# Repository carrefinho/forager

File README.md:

# Forager

Forager is a Voyager-inspired 34-key low-profile wireless split keyboard powered by ZMK.

> why does the large Voyager not simply eat the small Forager?

## Design

- Condensed [ZSA Voyager](https://www.zsa.io/voyager) layout without outer pinkie column and number row
- Hot-swap Kailh Choc V1 switches in Choc (18x17mm) spacing with Voyager-esque switch puller grooves

- Wireless only with Seeed XIAO nRF52840 running ZMK firmware
- Magnetic tenting legs inspired by Voyager and [Unicorne](https://www.boardsource.xyz/products/unicorne)

- Compact silhouette without the usual blank space occupied by controller
- Fully enclosed with 3D-printed two-piece case
- Minimal BOM by utilizing XIAO nRF52840's onboard RGB LED and reset button

## Build Guide and Parts List

[Find the build guide here.](/docs/build-guide.md)

## Firmware

[Find the ZMK module here.](https://github.com/carrefinho/forager-zmk-module)

## Credits

- [ZSA Voyager](https://www.zsa.io/voyager): overall layout & aesthetics
- [GEIGEIGEIST/TOTEM](https://github.com/GEIGEIGEIST/TOTEM): XIAO PCB footprint and general placement
- [ebastler/marbastlib](https://github.com/ebastler/marbastlib): symbols and PCB footprints
- [caksoylar/zmk-rgbled-widget](https://github.com/caksoylar/zmk-rgbled-widget): RGB LED functionality

## Gallery

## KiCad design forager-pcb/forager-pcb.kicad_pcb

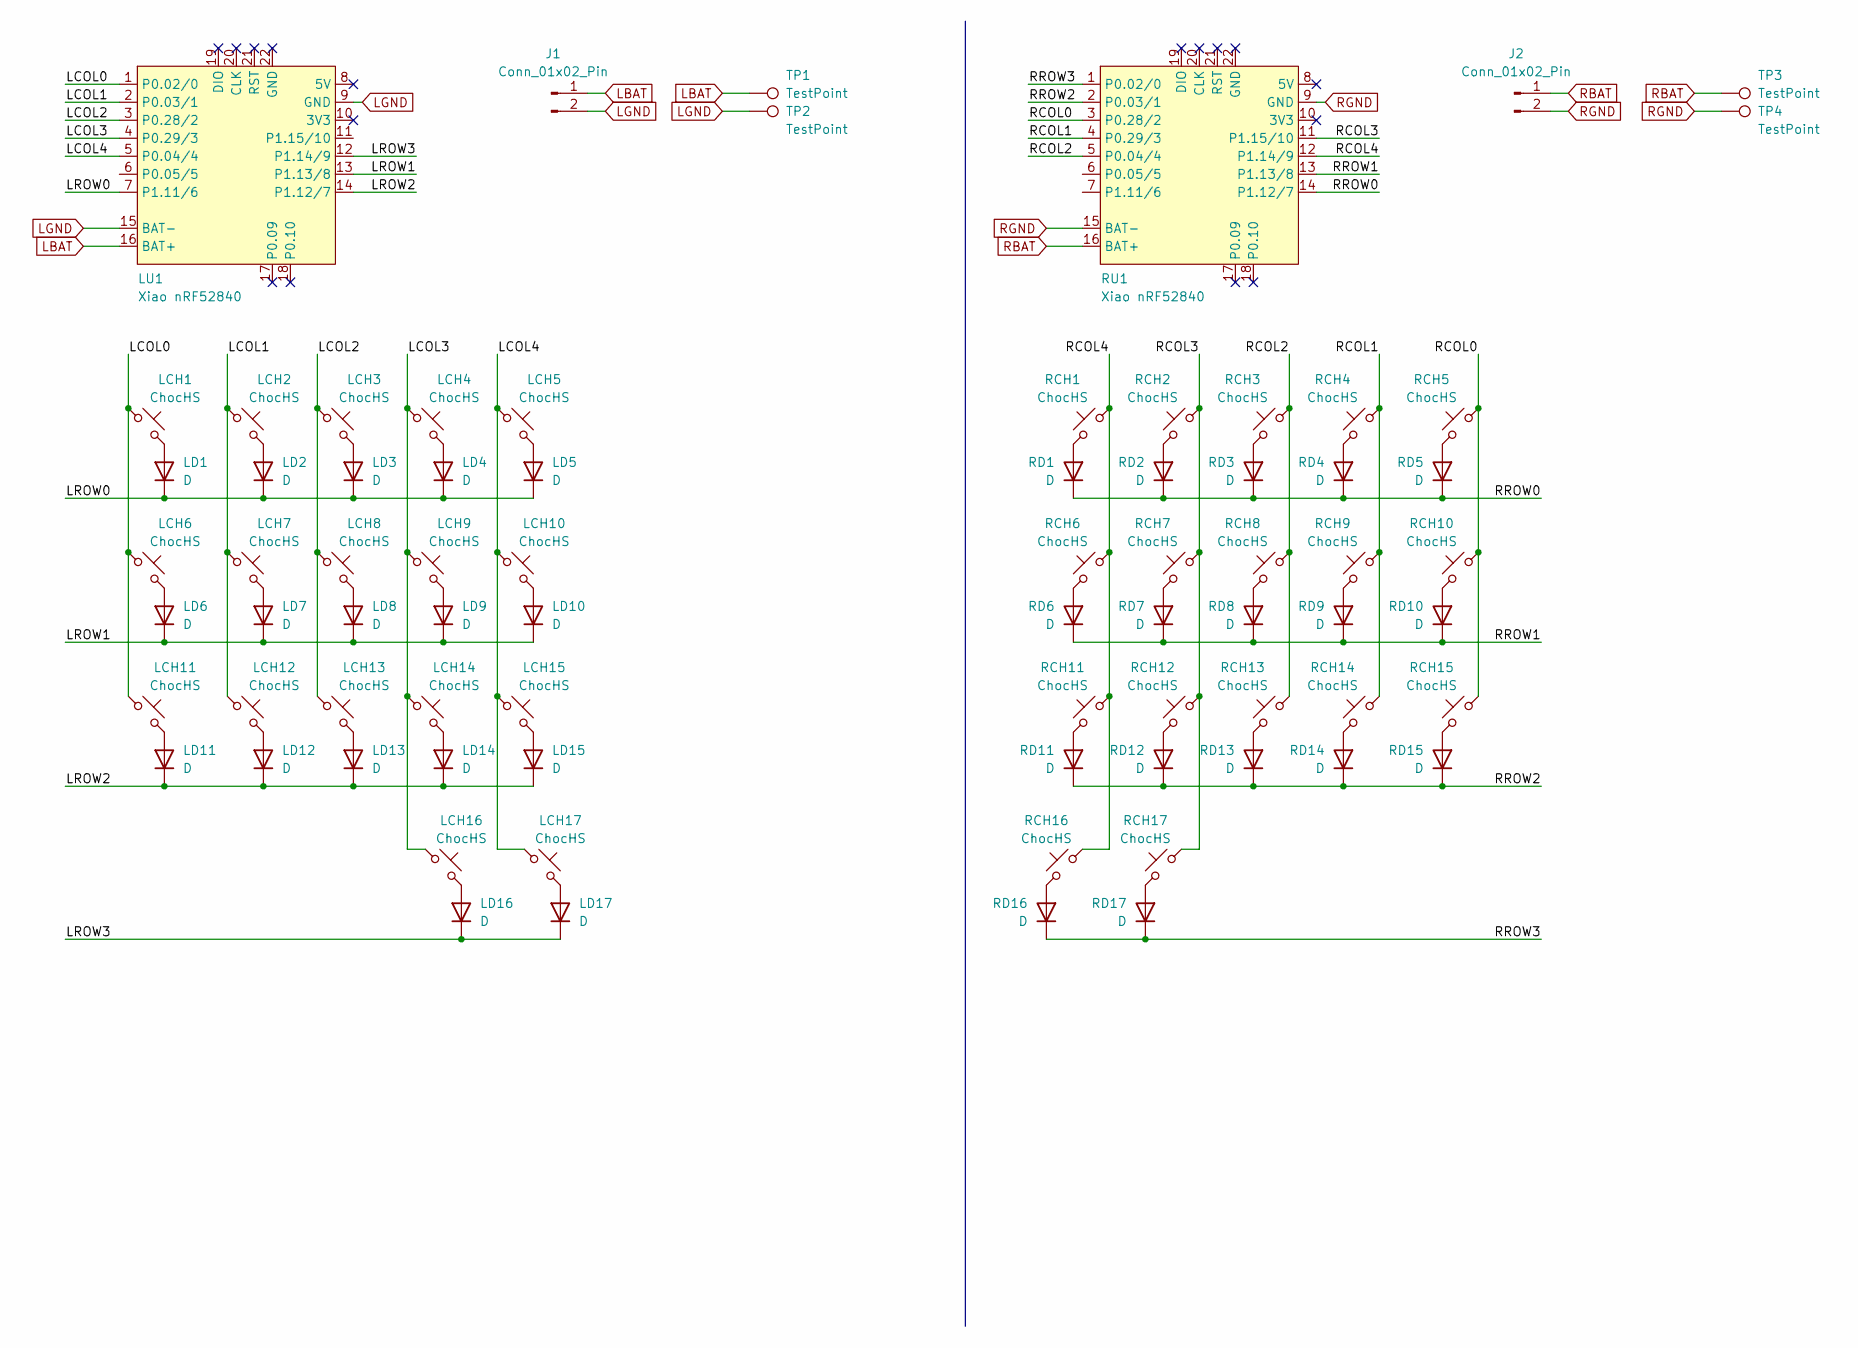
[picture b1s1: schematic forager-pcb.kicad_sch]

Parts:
J1, J2: Conn_01x02_Pin; JST_ACH_BM02B-ACHSS-GAN-ETF_1x02-1MP_P1.20mm_Vertical
LCH1, LCH2, LCH3, LCH4, LCH5, LCH6, LCH7, LCH8, LCH9, LCH10, LCH11, LCH12, LCH13, LCH14, LCH15, LCH16, LCH17: ChocHS; SW_choc_v1_HS_MBK
LD1, LD2, LD3, LD4, LD5, LD6, LD7, LD8, LD9, LD10, LD11, LD12, LD13, LD14, LD15, LD16, LD17: D; D_SOD-123
LU1: Xiao nRF52840; xiao-ble-smd-cutout
RCH1, RCH2, RCH3, RCH4, RCH5, RCH6, RCH7, RCH8, RCH9, RCH10, RCH11, RCH12, RCH13, RCH14, RCH15, RCH16, RCH17: ChocHS; SW_choc_v1_HS_MBK
RD1, RD2, RD3, RD4, RD5, RD6, RD7, RD8, RD9, RD10, RD11, RD12, RD13, RD14, RD15, RD16, RD17: D; D_SOD-123
RU1: Xiao nRF52840; xiao-ble-smd-cutout
TP1, TP2, TP3, TP4: TestPoint; TestPoint_Pad_D2.0mm

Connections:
/LCOL0: LCH1.1, LCH6.1, LCH11.1, LU1.1 (P0.02/0)
/LCOL1: LCH2.1, LCH7.1, LCH12.1, LU1.2 (P0.03/1)
/LCOL2: LCH3.1, LCH8.1, LCH13.1, LU1.3 (P0.28/2)
/LCOL3: LCH4.1, LCH9.1, LCH14.1, LCH16.1, LU1.4 (P0.29/3)
/LCOL4: LCH5.1, LCH10.1, LCH15.1, LCH17.1, LU1.5 (P0.04/4)
/LROW0: LD1.1 (K), LD2.1 (K), LD3.1 (K), LD4.1 (K), LD5.1 (K), LU1.7 (P1.11/6)
/LROW1: LD6.1 (K), LD7.1 (K), LD8.1 (K), LD9.1 (K), LD10.1 (K), LU1.13 (P1.13/8)
/LROW2: LD11.1 (K), LD12.1 (K), LD13.1 (K), LD14.1 (K), LD15.1 (K), LU1.14 (P1.12/7)
/LROW3: LD16.1 (K), LD17.1 (K), LU1.12 (P1.14/9)
/RCOL0: RCH5.1, RCH10.1, RCH15.1, RU1.3 (P0.28/2)
/RCOL1: RCH4.1, RCH9.1, RCH14.1, RU1.4 (P0.29/3)
/RCOL2: RCH3.1, RCH8.1, RCH13.1, RU1.5 (P0.04/4)
/RCOL3: RCH2.1, RCH7.1, RCH12.1, RCH17.1, RU1.11 (P1.15/10)
/RCOL4: RCH1.1, RCH6.1, RCH11.1, RCH16.1, RU1.12 (P1.14/9)
/RROW0: RD1.1 (K), RD2.1 (K), RD3.1 (K), RD4.1 (K), RD5.1 (K), RU1.14 (P1.12/7)
/RROW1: RD6.1 (K), RD7.1 (K), RD8.1 (K), RD9.1 (K), RD10.1 (K), RU1.13 (P1.13/8)
/RROW2: RD11.1 (K), RD12.1 (K), RD13.1 (K), RD14.1 (K), RD15.1 (K), RU1.2 (P0.03/1)
/RROW3: RD16.1 (K), RD17.1 (K), RU1.1 (P0.02/0)
LBAT: J1.1, LU1.16 (BAT+), TP1.1
LGND: J1.2, LU1.9 (GND), LU1.15 (BAT-), TP2.1
unnamed: LCH1.2, LD1.2 (A)
unnamed: LCH2.2, LD2.2 (A)
unnamed: LCH3.2, LD3.2 (A)
unnamed: LCH4.2, LD4.2 (A)
unnamed: LCH5.2, LD5.2 (A)
unnamed: LCH6.2, LD6.2 (A)
unnamed: LCH7.2, LD7.2 (A)
unnamed: LCH8.2, LD8.2 (A)
unnamed: LCH9.2, LD9.2 (A)
unnamed: LCH10.2, LD10.2 (A)
unnamed: LCH11.2, LD11.2 (A)
unnamed: LCH12.2, LD12.2 (A)
unnamed: LCH13.2, LD13.2 (A)
unnamed: LCH14.2, LD14.2 (A)
unnamed: LCH15.2, LD15.2 (A)
unnamed: LCH16.2, LD16.2 (A)
unnamed: LCH17.2, LD17.2 (A)
unnamed: RCH1.2, RD1.2 (A)
unnamed: RCH2.2, RD2.2 (A)
unnamed: RCH3.2, RD3.2 (A)
unnamed: RCH4.2, RD4.2 (A)
unnamed: RCH5.2, RD5.2 (A)
unnamed: RCH6.2, RD6.2 (A)
unnamed: RCH7.2, RD7.2 (A)
unnamed: RCH8.2, RD8.2 (A)
unnamed: RCH9.2, RD9.2 (A)
unnamed: RCH10.2, RD10.2 (A)
unnamed: RCH11.2, RD11.2 (A)
unnamed: RCH12.2, RD12.2 (A)
unnamed: RCH13.2, RD13.2 (A)
unnamed: RCH14.2, RD14.2 (A)
unnamed: RCH15.2, RD15.2 (A)
unnamed: RCH16.2, RD16.2 (A)
unnamed: RCH17.2, RD17.2 (A)
RBAT: J2.1, RU1.16 (BAT+), TP3.1
RGND: J2.2, RU1.9 (GND), RU1.15 (BAT-), TP4.1

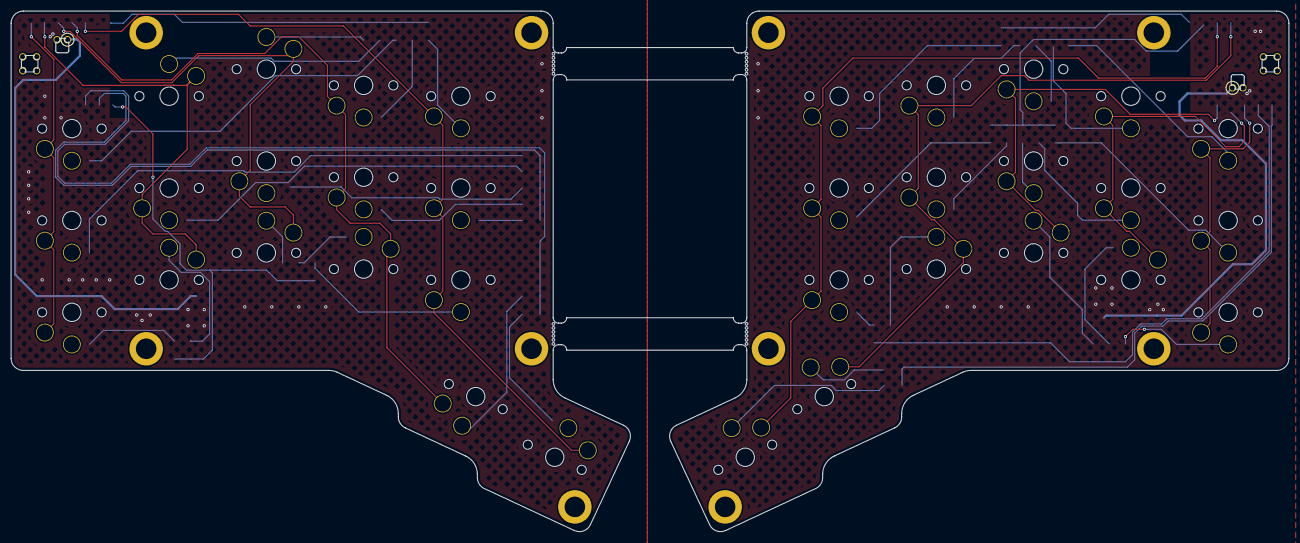
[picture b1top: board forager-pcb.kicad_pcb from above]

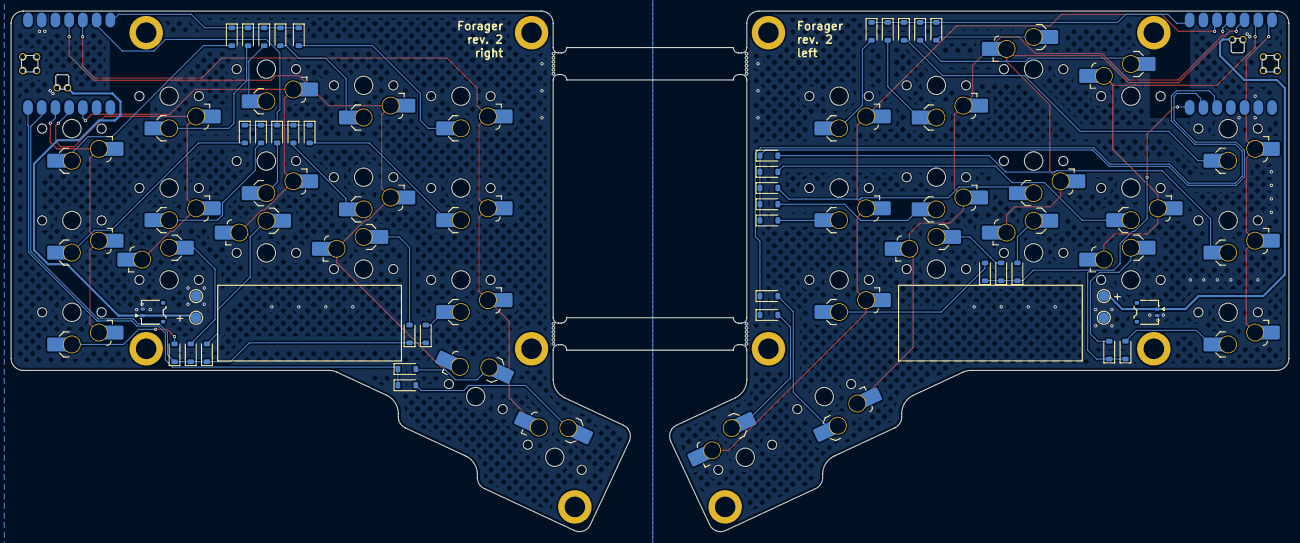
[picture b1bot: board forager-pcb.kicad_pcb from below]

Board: 2 copper layers, 236.5 x 96.3 mm, 76 parts (76 on the bottom side), 56 nets.

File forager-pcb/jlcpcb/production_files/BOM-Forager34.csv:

Comment,Designator,Footprint,LCSC
ChocHS,RCH16,SW_choc_v1_HS_MBK,
ChocHS,RCH6,SW_choc_v1_HS_MBK,
ChocHS,RCH10,SW_choc_v1_HS_MBK,
ChocHS,RCH14,SW_choc_v1_HS_MBK,
ChocHS,RCH2,SW_choc_v1_HS_MBK,
ChocHS,RCH9,SW_choc_v1_HS_MBK,
ChocHS,RCH12,SW_choc_v1_HS_MBK,
ChocHS,RCH7,SW_choc_v1_HS_MBK,
ChocHS,RCH13,SW_choc_v1_HS_MBK,
ChocHS,RCH5,SW_choc_v1_HS_MBK,
ChocHS,RCH8,SW_choc_v1_HS_MBK,
ChocHS,RCH11,SW_choc_v1_HS_MBK,
ChocHS,RCH4,SW_choc_v1_HS_MBK,
ChocHS,RCH15,SW_choc_v1_HS_MBK,
ChocHS,RCH17,SW_choc_v1_HS_MBK,
ChocHS,RCH3,SW_choc_v1_HS_MBK,
ChocHS,RCH1,SW_choc_v1_HS_MBK,
D,RD1,D_SOD-123,
D,RD17,D_SOD-123,
D,RD13,D_SOD-123,
D,RD5,D_SOD-123,
D,RD8,D_SOD-123,
D,RD2,D_SOD-123,
D,RD9,D_SOD-123,
D,RD12,D_SOD-123,
D,RD6,D_SOD-123,
D,RD7,D_SOD-123,
D,RD15,D_SOD-123,
Conn_01x02_Pin,J2,JST_ACH_BM02B-ACHSS-GAN-ETF_1x02-1MP_P1.20mm_Vertical,
D,RD16,D_SOD-123,
D,RD11,D_SOD-123,
D,RD3,D_SOD-123,
D,RD10,D_SOD-123,
D,RD14,D_SOD-123,
D,RD4,D_SOD-123,
D,LD12,D_SOD-123,
D,LD17,D_SOD-123,
ChocHS,LCH9,SW_choc_v1_HS_MBK,
D,LD9,D_SOD-123,
D,LD15,D_SOD-123,
D,LD4,D_SOD-123,
Conn_01x02_Pin,J1,JST_ACH_BM02B-ACHSS-GAN-ETF_1x02-1MP_P1.20mm_Vertical,
ChocHS,LCH2,SW_choc_v1_HS_MBK,
ChocHS,LCH7,SW_choc_v1_HS_MBK,
ChocHS,LCH4,SW_choc_v1_HS_MBK,
ChocHS,LCH11,SW_choc_v1_HS_MBK,
ChocHS,LCH13,SW_choc_v1_HS_MBK,
ChocHS,LCH3,SW_choc_v1_HS_MBK,
ChocHS,LCH8,SW_choc_v1_HS_MBK,
D,LD13,D_SOD-123,
ChocHS,LCH15,SW_choc_v1_HS_MBK,
ChocHS,LCH1,SW_choc_v1_HS_MBK,
D,LD7,D_SOD-123,
ChocHS,LCH6,SW_choc_v1_HS_MBK,
ChocHS,LCH12,SW_choc_v1_HS_MBK,
D,LD5,D_SOD-123,
ChocHS,LCH10,SW_choc_v1_HS_MBK,
ChocHS,LCH14,SW_choc_v1_HS_MBK,
D,LD1,D_SOD-123,
D,LD2,D_SOD-123,
D,LD11,D_SOD-123,
D,LD14,D_SOD-123,
D,LD16,D_SOD-123,
ChocHS,LCH17,SW_choc_v1_HS_MBK,
D,LD8,D_SOD-123,
D,LD3,D_SOD-123,
ChocHS,LCH5,SW_choc_v1_HS_MBK,
D,LD6,D_SOD-123,
ChocHS,LCH16,SW_choc_v1_HS_MBK,
D,LD10,D_SOD-123,

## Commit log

2024-07-25 add pcb files and license
2024-07-25 clean up pcb files
2024-07-25 update readme and add images
2024-07-25 add gerber file update readme add case files update pcb files
2024-07-26 update readme and add build guide
2024-07-26 fix typo and add firmware link.
2024-07-26 add tenting legs section
2024-07-26 fix readme formatting
2024-07-27 update docs and image
2024-07-27 update docs
2024-07-27 kicad: add antenna keepout zone
2024-07-28 update gerber with antenna keepout
2024-09-02 docs: update build guide and new photos
2024-09-02 docs: update photo
2024-09-02 docs: update image again
2024-09-03 docs: swap back photos
2024-09-05 docs: update credits
2024-09-05 docs: fix alt text typo
2024-09-10 docs: add image and update readme
2024-09-10 docs: better photos of reset button
2024-09-10 docs: move around photos once again
2024-09-10 docs: lower contrast photo of forager in white
2024-12-17 new photo and update docs
2024-12-17 update photo
2025-09-29 Save forager-pcb.kicad_pcb as forager-plus-pcb.kicad_pcb in KiCad v9.0.2
    This will be the Forager Plus PCB, direct wiring without diodes
    using the Seeed XIAO nRF52840 Plus controller which exposes 20
    GPIO pins using '9 extra 1.27mm pitch SMD castellation pins beyond
    standard XIAO nRF52840'.
2025-09-29 Remove all the old switch traces
2025-09-29 Set all the right hand switch diode nets to RGND
    Used sed to search and replace, and then opened and resaved in
    KiCad which renumbered the now much smaller list of nets:
    sed -i.bak 's/net .. "Net-(RD.*-A)/net 33 "RGND/g' forager-plus-pcb.kicad_pcb
2025-09-29 Set all left hand switch diode nets to LGND
    Again, used sed and then opened & saved in KiCad to renumber:
    sed -i.bak 's/net . "Net-(LD.*-A)/net 1 "LGND/g' forager-plus-pcb.kicad_pcb
    sed -i.bak 's/net .. "Net-(LD.*-A)/net 1 "LGND/g' forager-plus-pcb.kicad_pcb
2025-09-29 Remove left-over switch trace on right
2025-09-29 Swap switch column nets to zmk-helpers middle row style
    Changing to top/middle/bottom and thumbs to follow manually:
    sed -i.bak -e 's#"/RCOL0"#"RM4"#g' -e 's#"/RCOL1"#"RM3"#g' \
    -e 's#"/RCOL2"#"RM2"#g' -e 's#"/RCOL3"#"RM1"#g' \
    -e 's#"/RCOL4"#"RM0"#g' forager-plus-pcb.kicad_pcb
    sed -i.bak -e 's#"/LCOL0"#"LM4"#g' -e 's#"/LCOL1"#"LM3"#g' \
    -e 's#"/LCOL2"#"LM2"#g' -e 's#"/LCOL3"#"LM1"#g' \
2025-09-29 Use zmk-helpers LH1, LH0, RH0, RH1 for thumb nets
    Done manually in KiCad v9.0.2
2025-09-29 Use zmk-helpers LT*, LB*, RT* and RB* for top/bottom nets
    Done manually in KiCad v9.0.2
2025-09-29 Remove the original Seeed Xiao nRF52840 footprints (and nets)
    These only exposed 11 GPIO pins (plus 2 NFC pads on the back),
    not enough for direct wiring.
2025-09-29 Use Seeed XIAO nRF52840 Plus & hand wire switches (using both F&B)
    Using the Forager author's Seeed XIAO nRF52840 Plus footprint
    from https://github.com/carrefinho/visorbearer
    The plus pads do stick out slightly more than before and are on
    or over the top PCB edge. Should be fine...
    Note there is not quite enough clearance with the radio keepout
    to do single sided wiring (and thus potentially a reversible PCB
2025-09-30 Avoid D16 / P0.31 on Xiao nRF52840 Plus due to use in battery monitoring
    Also tweaked a few traces, lined up the vias etc.
2025-09-30 Start turning RHS into a reversible board
    This just doubles the controller footprint and addresses the
    controller wiring with vias. Switch footprints pending...
2025-09-30 Remove LHS leaving just single reversible board
2025-09-30 Column 4 now with reversible choc v1 switch footprints
    Using ceoloide's ergogen-footprints/switch_choc_v1_v2.js
    in v1 only mode (not enough space near controller for v2).
2025-10-01 More reversible switches
2025-10-01 Now all reversible switches - fighting ground plane
2025-10-01 Solved ground plane with explicit tracks
2025-10-01 Solved potential ground plane issue with explicit tracks
2025-10-02 Restore cutout and one set of 4 labels under USB
    These are CLK, DIO, GND, RST - can't connect GND due to mirroring
    with RST.
2025-10-02 Restore second set of 4 labels under USB
    These are CLK, DIO, GND, RST - can't connect GND due to mirroring
    with RST.
2025-10-02 Remove legacy BAT+ marker from original controller
2025-10-02 Battery connection with silkscreen (all on one footprint)
2025-10-02 Label pads D0 to D19 etc on silkscreen (one side so far)
2025-10-02 Combine F&B controller footprints (WIP)
2025-10-02 Combine F&B controller footprints (Still WIP)
2025-10-02 Fix up errors in tollerances for controller footprints
2025-10-03 Improve front/back balance; keep power on edge (for switch?)
2025-10-03 Shrink battery solder cutout
2025-10-03 clean
2025-10-03 Use alternative 3D model for Xiao nRF52840 plus
    https://www.printables.com/model/1338411-3d-model-for-seeed-studio-xiao-nrf52840-sense-plus/files
2025-10-03 Use 2-pin horizontal SMD PicoBlade MX 1.25mm battery connector.
    The inaccurate term JST 1.25mm, or 'Micro JST 1.25mm' is often
    used for these. The connector socket is under 4mm so should fit,
    and this is commonly offered as the connector with LiPo batteries.
    Putting this on both sides in place of the original (harder to
    find) connector and soldering points.
2025-10-03 Battery cutout by changing the PCB outline
2025-10-03 Adjust left/right labels and title on silkscreen
2025-10-03 Move battery connector forward to avoid bottom case rib
2025-10-09 Add MSK12C02 power switch - LCSC C431540 or similar, SMD
    These should both be up off (towards controller corner), and
    down on (away from controller). Ought to be able to solder
    bridge the pads if not using the switch?
    Hat tip https://github.com/letmegobacktosleep/forager/tree/power-switch/forager-pcb
    Using same location, so same case modifications should work.
2025-10-09 Move battery connector back (for plug); thru-hole solder points,
    I rotated the battery connection and moved back to give more clearance
    for the plug - beware the bottom case rib.
    Hat tip https://github.com/letmegobacktosleep/forager/tree/power-switch/forager-pcb
    for the thru-hole solder point idea, which seems a little easier to use.
2025-10-09 Fix offset for 3D model of case, drop use of original Xiao 3D model
2025-10-09 Lengthen battery cutout by 1mm
2025-10-09 Show 35x15mm battery cutout on user-drawings layer
2025-10-09 Remove left over silkscreen labels from old battery connector location
2025-10-10 Enlarge most 2x2.6mm hotswap pads to 2.6x2.6mm
    This is more symetric and more closely matches the original Forager
    hotswap footprint. Unclear why the Ceoloide Ergogen hotswaps are
    that small on one side - although they work fined fine for me as is
    on another board.
    The one by the battery cutout is still small.
2025-10-21 Save forager-pcb.kicad_pcb as forager-ph.kicad_pcb in KiCad v9.0.2
    This will be the Forager Partial Heawood or "Acid" PCB, still using
    the Seeed XIAO nRF52840 Plus controller but also the two NFC pads
    for 11+2 GPIOs for a diode-free reversible Graph Theory wiring.
2025-10-21 Remove all the old switch traces, set nets for direct wiring
    Set all the right hand switch diode nets to RGND
    Used sed to search and replace, and then opened and resaved in
    KiCad which renumbered the now much smaller list of nets:
    sed -i.bak 's/net .. "Net-(RD.*-A)/net 33 "RGND/g' forager-plus-pcb.kicad_pcb
    Set all left hand switch diode nets to LGND. Again, used sed
    and then opened & saved in KiCad to renumber:
2025-10-21 Make into a reversible board (replace switches in right, delete left)
    Double sided using original Xiao BLE (11+2 GPIOs), wiring to follow.
    Using ceoloide's ergogen-footprints/switch_choc_v1_v2.js footprint
    in v1 only mode (not enough space near controller for v2).
    Use 2-pin horizontal SMD PicoBlade MX 1.25mm battery connector.
    The inaccurate term JST 1.25mm, or 'Micro JST 1.25mm' is often
    used for these. The connector socket is under 4mm so should fit,
2025-10-21 Use XIAO-nRF52840 v15.step
    See https://files.seeedstudio.com/wiki/XIAO-BLE/seeed-studio-xiao-nrf52840-3d-model.zip
    from https://wiki.seeedstudio.com/XIAO_BLE/#seeed-studio-xiao-nrf52840
2025-10-21 Add P0.09 and P0.10 NFC pads to footprint
    These are in the wireless keepout (sigh), and P0.10 is so tight in the
    corner it will be tricky.
2025-10-21 Partial Heawood Graph Theory diode-free switch wiring done
2025-10-21 Add bonus sideways SMD thumb switch to fill out the matrix.
    This will need a tiny case mode, and perhaps a longer than usual button
    if this isn't close enough to the edge? Vertical position limited by
    bottom case rib.
    Wiring required a few more vias for the ground plane.
2025-10-21 Add MSK12C02 power switch - LCSC C431540 or similar, SMD
    These should both be up off (towards controller corner), and
    down on (away from controller). Ought to be able to solder
    bridge the pads if not using the switch?
    Hat tip https://github.com/letmegobacktosleep/forager/tree/power-switch/forager-pcb
2025-10-21 Graph Theory Silkscreen art using Heawood Graph
2025-10-21 Rotate battery connection and move back to give clearance,
    Beware the bottom case ribs...
2025-10-21 Lengthen battery cutout
2025-10-21 Show 15x35mm battery placeholder
2025-10-21 Restore direct solder points for battery connection
2025-10-21 Enlarge most 2x2.6mm hotswap pads to 2.6x2.6mm
    This is more symetric and more closely matches the original Forager
    hotswap footprint. Unclear why the Ceoloide Ergogen hotswaps are
    that small on one side - although they work fined fine for me as is
    on another board.
    A few are still on the small side due to constaints like the battery
    cut out, or wiring.
2025-10-21 Change to thru-hole battery terminals for direct solder option
    Hat tip https://github.com/letmegobacktosleep/forager/tree/power-switch/forager-pcb
2025-10-21 Set title and revision: Forager Acid 1.0.0
2025-10-21 Gerbers for Forager Acid 1.0.0
